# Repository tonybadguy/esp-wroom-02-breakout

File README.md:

# esp-wroom-02-breakout
A breakout board for the Arduino-compatible Espressif ESP-WROOM-02 module.

* Designed with connectors for use on a breadboard
* Because the module is wide, the narrow width of the breakout board frees up more room for connections on the breadboard
* Connectors follow the same relative ordering as the module contacts (although it is reversed)

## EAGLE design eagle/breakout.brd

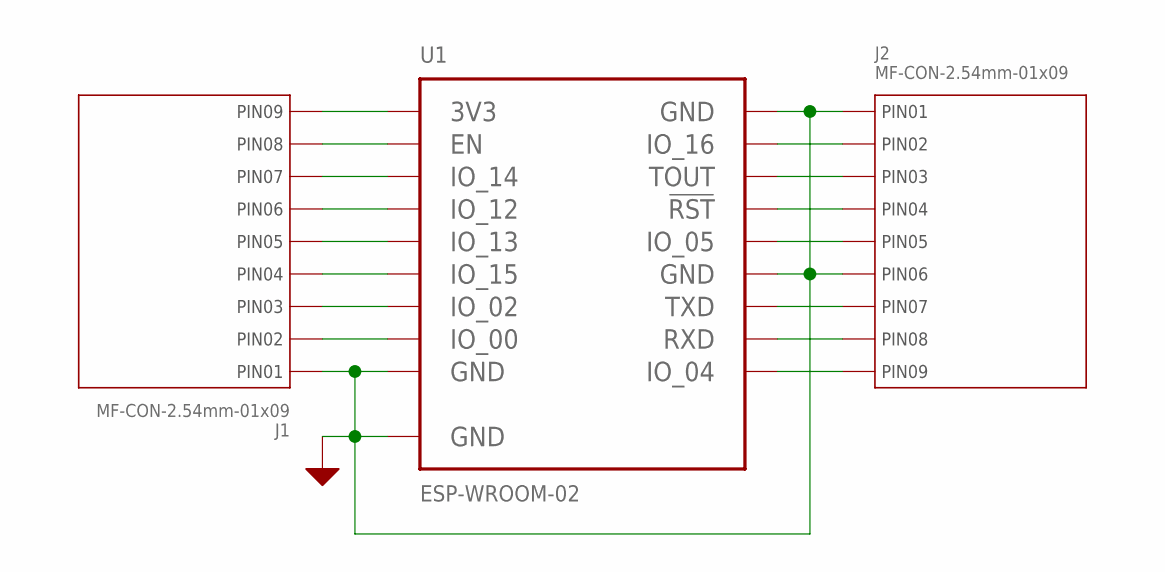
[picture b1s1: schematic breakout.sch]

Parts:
J1, J2: MF-CON-2.54mm-01x09; PTH_2.54MM_01X09
U1: ESP-WROOM-02

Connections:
GND: J1.P$1 (PIN1), J2.P$1 (PIN1), J2.P$6 (PIN6), U1.GND, U1.GND@9 (GND), U1.GND@13 (GND), U1.GND@18 (GND)
unnamed: J1.P$9 (PIN9), U1.3V3
unnamed: J1.P$8 (PIN8), U1.EN
unnamed: J1.P$7 (PIN7), U1.IO_14
unnamed: J1.P$6 (PIN6), U1.IO_12
unnamed: J1.P$5 (PIN5), U1.IO_13
unnamed: J1.P$4 (PIN4), U1.IO_15
unnamed: J1.P$3 (PIN3), U1.IO_02
unnamed: J1.P$2 (PIN2), U1.IO_00
unnamed: J2.P$2 (PIN2), U1.IO_16
unnamed: J2.P$3 (PIN3), U1.TOUT
unnamed: J2.P$4 (PIN4), U1.RST (!RST)
unnamed: J2.P$5 (PIN5), U1.IO_05
unnamed: J2.P$7 (PIN7), U1.TXD
unnamed: J2.P$8 (PIN8), U1.RXD
unnamed: J2.P$9 (PIN9), U1.IO_04

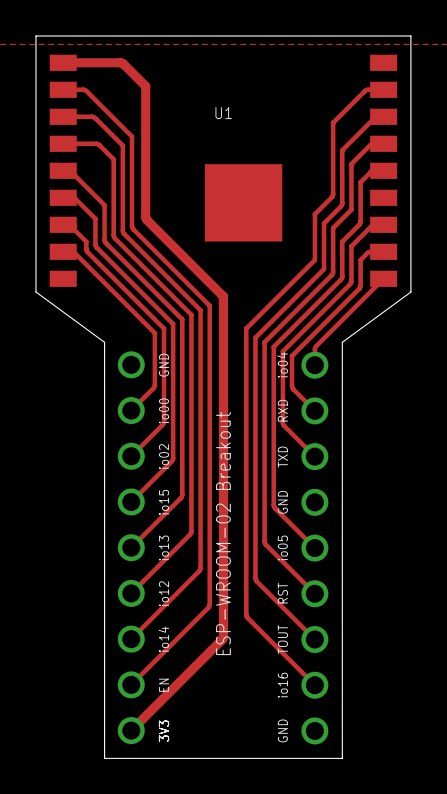
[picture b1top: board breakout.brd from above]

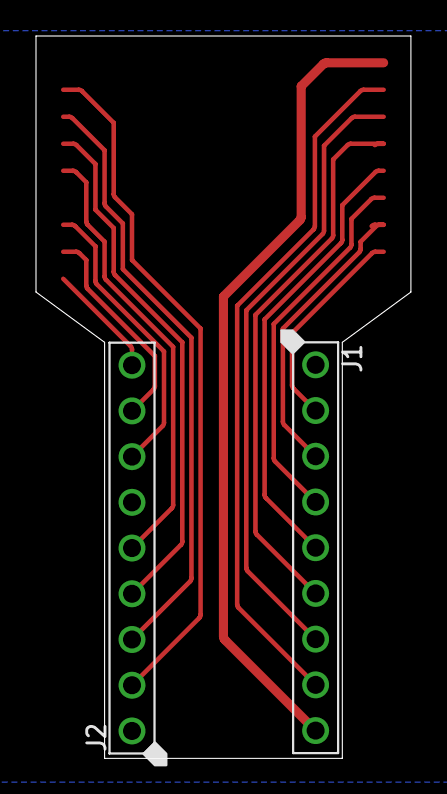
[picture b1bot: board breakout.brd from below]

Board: 2 copper layers, 20.8 x 40.1 mm, 3 parts (2 on the bottom side), 16 nets.

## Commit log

2018-03-07 images
2018-04-06 added photo
